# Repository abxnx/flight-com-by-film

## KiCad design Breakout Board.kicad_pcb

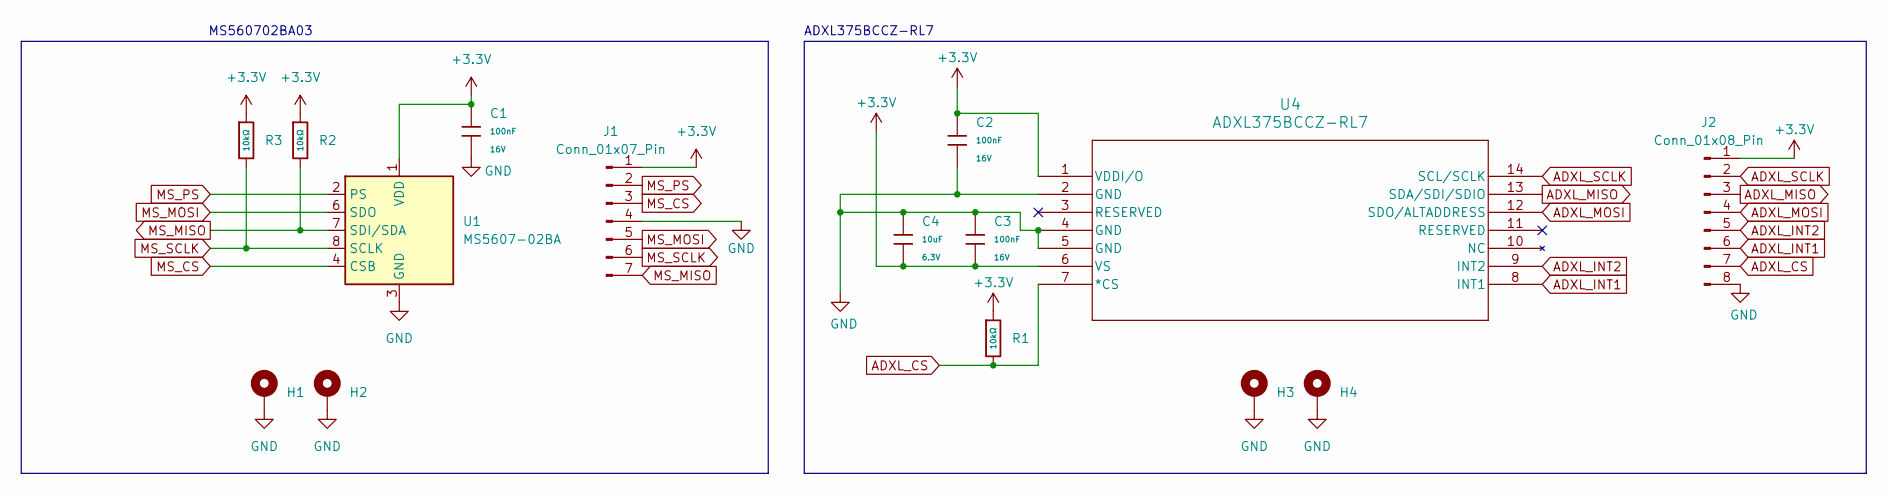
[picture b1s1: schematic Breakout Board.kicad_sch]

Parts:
C1, C2, C3: 100nF; C_0805; Voltage Rated 16V; Tolerance ±10%; Part CL05B104KO5NNNC; LCSC C1525
C4: 10uF; C_0805; Voltage Rated 6.3V; Tolerance ±20%; Part CL05A106MQ5NUNC; LCSC C15525
H1, H2, H3, H4: MountingHole_Pad; MountingHole_2.2mm_M2_DIN965_Pad
J1: Conn_01x07_Pin; PinHeader_1x07_P2.54mm_Vertical
J2: Conn_01x08_Pin; PinHeader_1x08_P2.54mm_Vertical
R1, R2, R3: 10kΩ; R_0805; Overload Voltage (Max) 50V; Tolerance ±1%; Part 0402WGF1002TCE; LCSC C25744
U1: MS5607-02BA; LGA-8_3x5mm_P1.25mm
U4: ADXL375BCCZ-RL7; LGA_CC-14-1_ADI

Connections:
+3.3V: C1.1, C2.1, C3.2, C4.2, J1.1, J2.1, R1.1, R2.1, R3.1, U1.1 (VDD), U4.1 (VDDI/O), U4.6 (VS)
ADXL_CS: J2.7, R1.2, U4.7 (*CS)
ADXL_INT1: J2.6, U4.8 (INT1)
ADXL_INT2: J2.5, U4.9 (INT2)
ADXL_MISO: J2.3, U4.13 (SDA/SDI/SDIO)
ADXL_MOSI: J2.4, U4.12 (SDO/ALTADDRESS)
ADXL_SCLK: J2.2, U4.14 (SCL/SCLK)
GND: C1.2, C2.2, C3.1, C4.1, H1.1, H2.1, H3.1, H4.1, J1.4, J2.8, U1.3 (GND), U4.2 (GND), U4.4 (GND), U4.5 (GND)
MS_CS: J1.3, U1.4 (CSB), U1.5 (CSB)
MS_MISO: J1.7, R2.2, U1.7 (SDI/SDA)
MS_MOSI: J1.5, U1.6 (SDO)
MS_PS: J1.2, U1.2 (PS)
MS_SCLK: J1.6, R3.2, U1.8 (SCLK)

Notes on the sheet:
ADXL375BCCZ-RL7
MS560702BA03

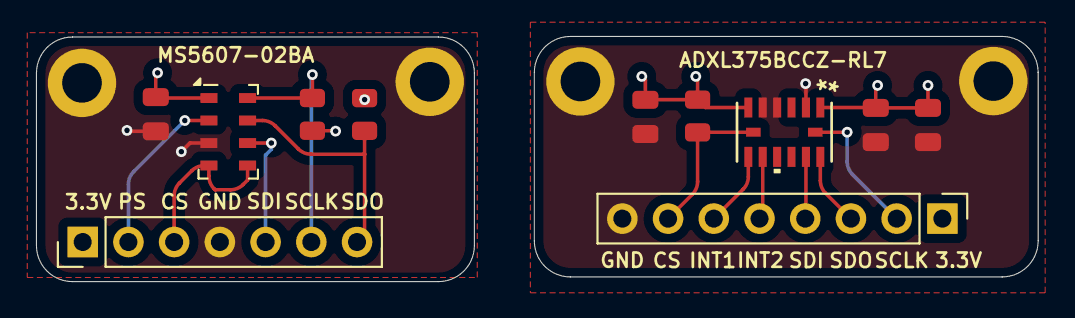
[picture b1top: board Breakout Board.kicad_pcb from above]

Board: 4 copper layers, 55.6 x 13.6 mm, 15 parts (0 on the bottom side), 13 nets.

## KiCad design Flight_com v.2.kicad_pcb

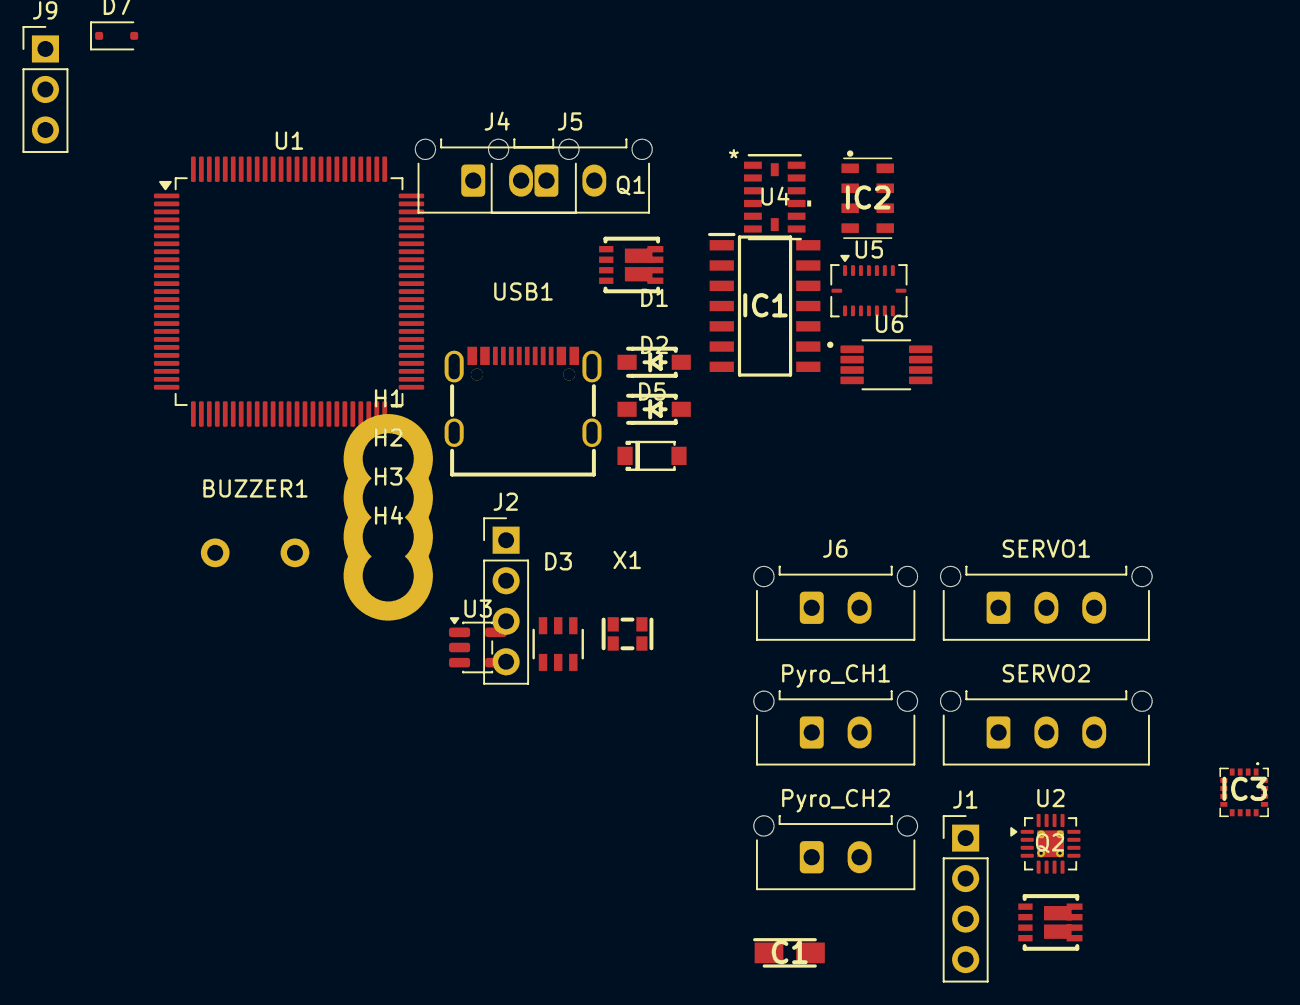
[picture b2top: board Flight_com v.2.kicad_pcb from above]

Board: 2 copper layers, 34 parts (0 on the bottom side), 40 nets, no tracks yet.

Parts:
BUZZER1: PS1240P02BT; BUZ-TH_BD12.5-P5.00-D0.9
C1: F930J107MAA; CAPPM3216X180N
D1, D2: NRVB120VLSFT1G; SOD-123_L2.7-W1.6-LS3.7-RD-1
D3: USBLC6-2SC6; SOT-23-6_L2.9-W1.6-P0.95-LS2.8-BL
D5: MMSZ4683T1G; SOD-123_L2.8-W1.8-LS3.7-RD
D7: PMEG2005EJ; D_SOD-323F
H1, H2, H3, H4: MountingHole_Pad; MountingHole_3.2mm_M3_DIN965_Pad
IC1: SN74HCT125DRG4; SOIC127P600X175-14N
IC2: MS560702BA03-50; MS5607-02BA03
IC3: MMC5983MA
J1: Companion; PinHeader_1x04_P2.54mm_Vertical
J2: SWD; PinHeader_1x04_P2.54mm_Vertical
J4, J5, J6: Molex Microfit; Molex_Micro-Fit_3.0_43650-0215_1x02_P3.00mm_Vertical
J9: Conn_01x03_Pin; PinHeader_1x03_P2.54mm_Vertical
Pyro_CH1, Pyro_CH2: Molex Microfit; Molex_Micro-Fit_3.0_43650-0215_1x02_P3.00mm_Vertical
Q1, Q2: SI7232DN-T1-GE3; POWER-1212-8_L3.3-W3.3-P0.66-LS3.3-BL
SERVO1, SERVO2: Conn_01x03_Pin; Molex_Micro-Fit_3.0_43650-0315_1x03_P3.00mm_Vertical
U1: STM32U575VGTx; LQFP-100_14x14mm_P0.5mm
U2: TPS62153; VQFN-16-1EP_3x3mm_P0.5mm_EP1.68x1.68mm_ThermalVias
U3: TLV75733PDBV; SOT-23-5
U4: ADXL375BCCZ-RL7; LGA_CC-14-1_ADI
U5: BMI088; Bosch_LGA-16_4.5x3mm_P0.5mm_LayoutBorder7x1y_ClockwisePinNu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
U6: TMP275AIDGKR; SOP65P490X110-8N
USB1: TYPE-C-2.0-16PIN-SMT-3; TYPE-C-SMD_TYPE-CF3.1
X1: 1XXD32000MBA; OSC-SMD_4P-L2.0-W1.6-BL_1XXD

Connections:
+3.3V: D7.2 (A), IC2.1 (VDD), IC3.2 (VDD), IC3.4 (SPI_CS), IC3.13 (VDDIO), J1.1, J2.1, U3.5 (OUT), U4.1 (VDDI/O), U4.6 (VS), U5.3 (VDD), U5.11 (VDDIO), U6.8 (V+), X1.4 (VCC)
+5V: C1.1 (+), D2.2 (A), IC1.14 (VCC), J4.2, U2.14 (VOS)
/PWM_PD: IC1.1 (1~OE), IC1.4 (2~OE), IC1.10 (3~OE), IC1.13 (4~OE)
ADXL_CS: U1.68 (PA9), U4.7 (*CS)
ADXL_INT1: U1.83 (PD2), U4.8 (INT1)
ADXL_INT2: U1.84 (PD3), U4.9 (INT2)
ADXL_MISO: U1.79 (PC11), U1.80 (PC12), U4.13 (SDA/SDI/SDIO)
ADXL_SCLK: IC2.8 (SCLK), U1.78 (PC10), U4.14 (SCL/SCLK)
BMI_Accel_CS: U1.55 (PD8), U5.14 (~CSB1)
BMI_Accel_INT1: U1.64 (PC7), U5.16 (INT1)
BMI_Accel_INT2: U1.65 (PC8), U5.1 (INT2)
BMI_GYRO_CS: U1.56 (PD9), U5.5 (~CSB2)
BMI_Gyro_INT1: U1.81 (PD0), U5.12 (INT3)
BMI_Gyro_INT2: U1.82 (PD1), U5.13 (INT4)
BMI_MISO: U1.53 (PB14), U5.10 (SDO2), U5.15 (SDO1)
BMI_MOSI: U1.54 (PB15), U5.9 (SDI/SDA)
BMI_SCK: U1.52 (PB13), U5.8 (SCK/SCL)
D+: D3.1, USB1.A6 (DP1), USB1.B6 (DP2)
D-: D3.3, USB1.A7 (DN1), USB1.B7 (DN2)
MMC_INT: IC3.15 (INT), U1.91 (PB5)
MMC_SCK: IC3.1 (SCL/SPI_SCK), U1.92 (PB6)
MMC_SDA: IC3.16 (SDA/SPI_SDI), U1.93 (PB7)
MS_CS: IC2.5 (CSB_2), U1.67 (PA8)
unnamed: BUZZER1.1, Q2.5 (D2), Q2.6 (D2)
unnamed: U2.1 (SW), U2.2 (SW), U2.3 (SW)
unnamed: Pyro_CH1.2, Q1.7 (D1), Q1.8 (D1)
unnamed: Pyro_CH2.2, Q1.5 (D2), Q1.6 (D2)
unnamed: U1.10 (VSS), U1.27 (VSS), U1.49 (VSS), U1.74 (VSS), U1.99 (VSS)
PWM_D: IC1.9 (3A), IC1.12 (4A)
PYRO: J5.2, Pyro_CH1.1, Pyro_CH2.1
PYRO_A: IC1.3 (1Y), Q1.2 (G1)
PYRO_B: C1.2 (-), D3.2, D5.2 (A), H1.1, H2.1, H3.1, H4.1, IC1.6 (2Y), IC1.7 (GND), IC2.2 (PS), IC2.3 (GND), IC3.9 (GND_1), IC3.11 (GND_2), J1.4, J2.4, J4.1, J5.1, J6.1, J9.3, Q1.1 (S1), Q1.3 (S2), Q1.4 (G2), Q2.3 (S2), SERVO1.3, SERVO2.3, U2.5 (FB), U2.6 (GND), U2.7 (FSW), U2.8 (DEF), U2.15 (GND), U2.16 (GND), U2.17 (GND), U3.2 (GND), U4.2 (GND), U4.4 (GND), U4.5 (GND), U5.2 (GNDA), U5.4 (GNDA), U5.6 (GNDIO), U5.7 (PS), U6.4 (GND), U6.5 (A2), U6.6 (A1), U6.7 (A0), USB1.1 (EH), USB1.A1 (GND), USB1.A12 (GND), USB1.B1 (GND), USB1.B12 (GND), X1.1 (GND), X1.2 (GND)
SERVO_B: IC1.8 (3Y), IC1.11 (4Y), SERVO2.1
ServoPow: J6.2, SERVO1.2, SERVO2.2
TMP_ALERT: U1.58 (PD11), U6.3 (ALERT)
TMP_SCL: U1.59 (PD12), U6.2 (SCL)
TMP_SDA: U1.60 (PD13), U6.1 (SDA)
VBAT+: U2.10 (VIN), U2.11 (VIN), U2.12 (VIN), U2.13 (EN)
VBUS: D1.2 (A), D3.5, USB1.A4 (VBUS), USB1.A9 (VBUS), USB1.B4 (VBUS), USB1.B9 (VBUS)
VBUSout: D1.1 (K), D2.1 (K), U3.1 (IN), U3.3 (EN)

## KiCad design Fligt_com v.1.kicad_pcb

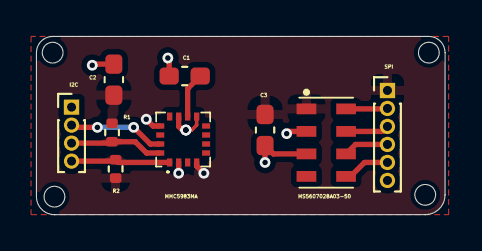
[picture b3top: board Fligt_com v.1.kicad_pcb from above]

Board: 2 copper layers, 22.7 x 9.9 mm, 13 parts (0 on the bottom side), 10 nets.

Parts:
1u1, 10u1, 100n1: C; C_0603_1608Metric_Pad1.08x0.95mm_HandSolder
H1, H2, H3, H4: MountingHole; ToolingHole_1.152mm
IC1: MS560702BA03-50; MS5607-02BA03
IC2: MMC5983MA
J1: Conn_01x06_Pin; PinHeader_1x06_P1.00mm_Vertical
J2: Conn_01x04_Pin; PinHeader_1x04_P1.00mm_Vertical
R1, R2: 2.7k; R_0402_1005Metric

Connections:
+3.3V: 1u1.2, 100n1.2, IC1.1 (VDD), IC2.2 (VDD), IC2.4 (SPI_CS), IC2.13 (VDDIO), J1.1, R1.2, R2.1
GND: 1u1.1, 10u1.1, 100n1.1, IC1.2 (PS), IC1.3 (GND), IC2.9 (GND_1), IC2.11 (GND_2), J1.6, J2.1
INT: IC2.15 (INT), J2.2
MS5607_CS: IC1.5 (CSB_2), J1.5
unnamed: 10u1.2, IC2.10 (CAP)
SCK: IC2.1 (SCL/SPI_SCK), J2.4, R2.2
SCLK: IC1.8 (SCLK), J1.2
SDA: IC2.16 (SDA/SPI_SDI), J2.3, R1.1
SDI: IC1.7 (SDI/SDA), J1.3
SDO: IC1.6 (SDO), J1.4

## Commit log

2025-10-03 set up project
2025-10-09 Update avionics PCB schematic
2025-12-26 Resolve merge conflict: ignore fp-info-cache
2025-12-26 Remove KiCad v1 files from repo
2025-12-26 Remove backups folder from repo
2025-12-26 Remove build/backup artifacts
2025-12-26 Ignore .bak files
2025-12-26 Fix .gitignore (ignore Debug/backups/bak)
2025-12-26 Ignore fp-info-cache
2026-01-21 Add Breakout Board folder
